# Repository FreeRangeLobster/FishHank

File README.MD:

# Description
This embedded system is designed to control control devices used in a fish tank, thies Includes but is not limited to lights, filter pumps, air pumps, CO2 reactors, UV lights and others. The system is capable of controllng 8 channels 220V AC up to 2A each 

The system is also equiped with the following systems: 
	-SD card
	-Real time clock
	-Bluetooth connection
	-flash memory 
	-temperature sensor. 
	
This devices are available to be connected to any IOT terminal, which could be a Raspberry pi or a ESP32 or a ST Nucleo. for this iteration it was selected an ESP32 WRoom 32.

## Weapons of choice
Embedded System ESP32	: Visual Studio Code with platform IO
Aux IO Control syste 	: Visual Studio Code with platform IO
Supervisory system   	: Visual Studio .net C# and WPF
Supervisory system 		: Mosquitto and NodeRed- Running on Raspberry pi(Experimetal)
PCB Development     	: Eagle
Comms to 3rd party		: ESP32 TCP Server/Client
Fast prototyping    	:Arduino IDE 1.6
Source Control and housekeeping: GitHub 

## PCB BOM
See parts schedule file 

## Production Files
Files submited to produce PCB

## PCB
Schematic and PCB files. Developed using Eagle

## Supervisory and config App
Developed using c#

## Images
Schematic

PCB

Format: 

## Libraries
Libraries developed and downloaded for the pcb integration

RTC
GetTimeNumber
GetTimeString
SetTimeString
CalculateFutureTimeCheck

OLED
DrawTable
ShowStatus
ShowTemperature
ShowOutputs
ShowTime
InitialDisplayShow

SD
FindEvent(CurrentTime)
GetStatus
GetConfiguration
DumpEvents

INPUTOUTPUT CONTROLLER 
GetStatus
SetOutputTo(OutputNumber,State)
GetInputs
ClearEvent
ClearOutputs

## Export
This folder contains 1:1 export views of the PCB

## Datasheets
Datasheets of the components used in the PCB

## Arduino Code
Developed to test the SSRs and User Inputs

# To Do is To Be 
|Status|ID|Description|
| ------ | ------ | ------ |
|DONE|1|Populate and test the PSU, test for shrt circuit and protectionsn |
|DONE|2|Populate and test One channel the SSR system |DONE|
|DONE|3|Populate and test microcontroller |
|DONE|4|populate and test bluetooth DONE |
|DONE|5|sd card reader DONE |
|DONE|6|realtime clock DONE |
|DONE|7|Temperature DONE |
|DONE|8|Make APIs libraries to deal with peripherals |
|DONE|9|add ALL days event |
|DONE|10|Tidy up oled screen, clear display square before writing output |
|DONE|11|test bluetooth debugging messages|
|DONE|12|mod the arduino auc board to update and toggle output|
|DONE|13|add Auto/Manual switch to the controller|
||14|Apply loads and test outputs|
|DONE|15|Rearrange outputs in arduino aux|
|DONE|16|Read IOAux output state|
|DONE|17|Test using Bluetooth|
|DONE|18|Test Application|
||19|Add the leds to the NodeRed|
|DONE|20|Top acrilic cover to test mains|
||21|Modify and update PCB layout and components-See notes in logbook|
|DONE|22|Tidy up code, files and merge to master|
|DONE|24|Double check and record GPIOs schedule ESP32-DevKit| 
||25|Get enclosure out of fishtank and replace components|
||26||
||27||
||28||
||29||
||30||
||31||
||32||
||33||
||34||
||35||

# To Do is To Be Embedded system- Code implementation
| API | Function | Implemented | Tested Works | Doesnt work | Not Tested | Notes | 
| ------ | ------ | ------ | ------ | ------ | ------ | ----------------------------------- | 
|RTC  |GetTimeNumber 	| YES |YES|  |  |  |
|RTC  |GetTimeString 	| YES |YES|  |  |  |
|RTC  |SetTimeString 	| YES |YES|  |  |  |
|OLED |DrawTable     	|YES  |YES  |  |  |  |
|OLED |ShowStatus  		|YES|YES|  |  |  |
|OLED |ShowTemperature 	| YES |YES|  |  |  |
|OLED |ShowOutputs 		|YES  |YES|  |  |  |
|OLED |ShowTime 		|YES|YES |  |  |  |
|OLED |InitialDisplayShow | YES |YES |  |  |  |
|OLED |CalculateFutureTimeCheck | YES |YES  |  |  |  |
|SD   |FindEvent(CurrentTime) |YES|YES  |  |  |  |
|SD   |GetStatus		| YES |YES  |  |  |  |
|SD   |GetConfiguration	|  YES|YES  |  |  |  |
|SD   |DumpEvents		| YES 	| YES|  |  |  |
|IO Ctrl|GetStatus		| YES | YES |  |  |  |
|IO Ctrl|SetOutputTo(OutputNumber,State)| YES |YES  |  |  |  |
|IO Ctrl|ClearInputEvent| NA |  |  |  | NA as IOCtrl updates automatic   |
|IO Ctrl|ClearOutputs| NA|  |  |  | Covered in Set Output To |

# Commands
? Help
K Initialise
I Idle
N Update Screen
M Check Events
O Update Outputs
D Delete Memory
0 Read Page Number 0_0000
1 AddEvent  1_1030WED31
2 Disable Event  2_001
3 Trace ON
4 Update Output 4_11 Output 1 ON
5 Write Status on OLED 5_Hello
6 Set Time RTC 6_DDMMY_HHmmss
7 Read Time
8 Check Current Event
9 Trace OFF

# PCB Upgrades and Improvements
|Status|ID|Description|
| ------ | ------ | ------ |
||1|Remove JLCJLCJCL, manufacturer disregarded the notes |
||2|Git webpage is not legible, find a better place|
|DONE|3|Bluetooth pinout is back to front in the eagle pcb library|
||4|Transistor not BCE, evaluate to use another one- Wrong footprint|
|DONE|5|SSR Output changed to 150ohm for a 10K resistor, so far is working fine|
||6|Breakout connector pin 1 and 2 to be renamed. INT1-> 5V, INT2->3V|
||7|Footprint of SSR to be adjusted|
||8|Add level converters, BSS138|
||9|Add 2 additional LEDs to show stay alive signal|
||10|Change output numbers in PCB to make it more readable|
||11|Add ESP32-DevKit to the PCB|
||12|R_UTX1=Link, R_UTX2 = Not Fitted|
||13|Remove Flash memory|
||14|SD Card Feed 5V|
||15|Add Auto/Manual trhough the level converter|
|DONE|16|SD Card back to front|

### Cheatsheet
#### Git

Command | Description
--- | --- 
git fetch | gets the remote status of the repository
git status | display the local current status of the repository
git pull | updates changes in the local repository
git add . | updates (adds, removes) files and infor from local to remote repository
git commit -m "" | Commits the changes and allows for a message to be updated
git push origin master| Pushes changes to remote repository
git checkout --| Reverts the files to the last commited version
git reset --hard | UNDO local file changes and KEEP your last commit
 
git branch alphr | Creates a neew branch
git branch --list | List current branches
git checkout alphr | switch local head to printer
git branch | shows current branch
git push --set-upstream origin alphr| creates new branch and pushes to remote repository
git merge alphr| merges brench. first it is required to go to master by checkout master

special thanks to for the atmega library
https://github.com/njh/eagle-library
https://github.com/sparkfun/SparkFun-Eagle-Libraries

#### Controller Pins
Top View 

 Down conting from top - Right
GND    -> GND 
GPIO23 -> MOSI SD Card
GPIO22 -> I2C SCL Oled and RTC 
GPIO1  -> 
GPIO3  -> 
GPIO21 -> I2C SDA Oled and RTC
GND    -> 
GPIO19 -> MISO SD Card
GPIO18 -> CLK SD Card
GPIO5  -> Chip Select SD Card
GPIO17 -> Serial2 TX IO Controller 
GPIO16 -> Serial2 RX IO Controller
GPIO4  -> Serial2 RX Bluetooth
GPIO0  -> 
GPIO2  -> Serial2 TX Bluetooth
GPIO15 -> Temp 1 Wire
GPIO8  ->
GPIO7  ->
GPIO6  ->
3v3
USB Connection

down conting from top - Left
3v3    -> Level Shifter Power
EN     -> 
GPIO36 -> New Event IOCtrl
GPIO39 ->
GPIO34 ->
GPIO35 ->
GPIO32 ->
GPIO33 ->
GPIO25 ->
GPIO26 ->
GPIO27 -> 
GPIO14 ->
GPIO12 ->
GND    ->
GPIO13 ->
GPIO9  ->
GPIO10 ->
GPIO11 ->
VIN    -> 
USB Connection to PC

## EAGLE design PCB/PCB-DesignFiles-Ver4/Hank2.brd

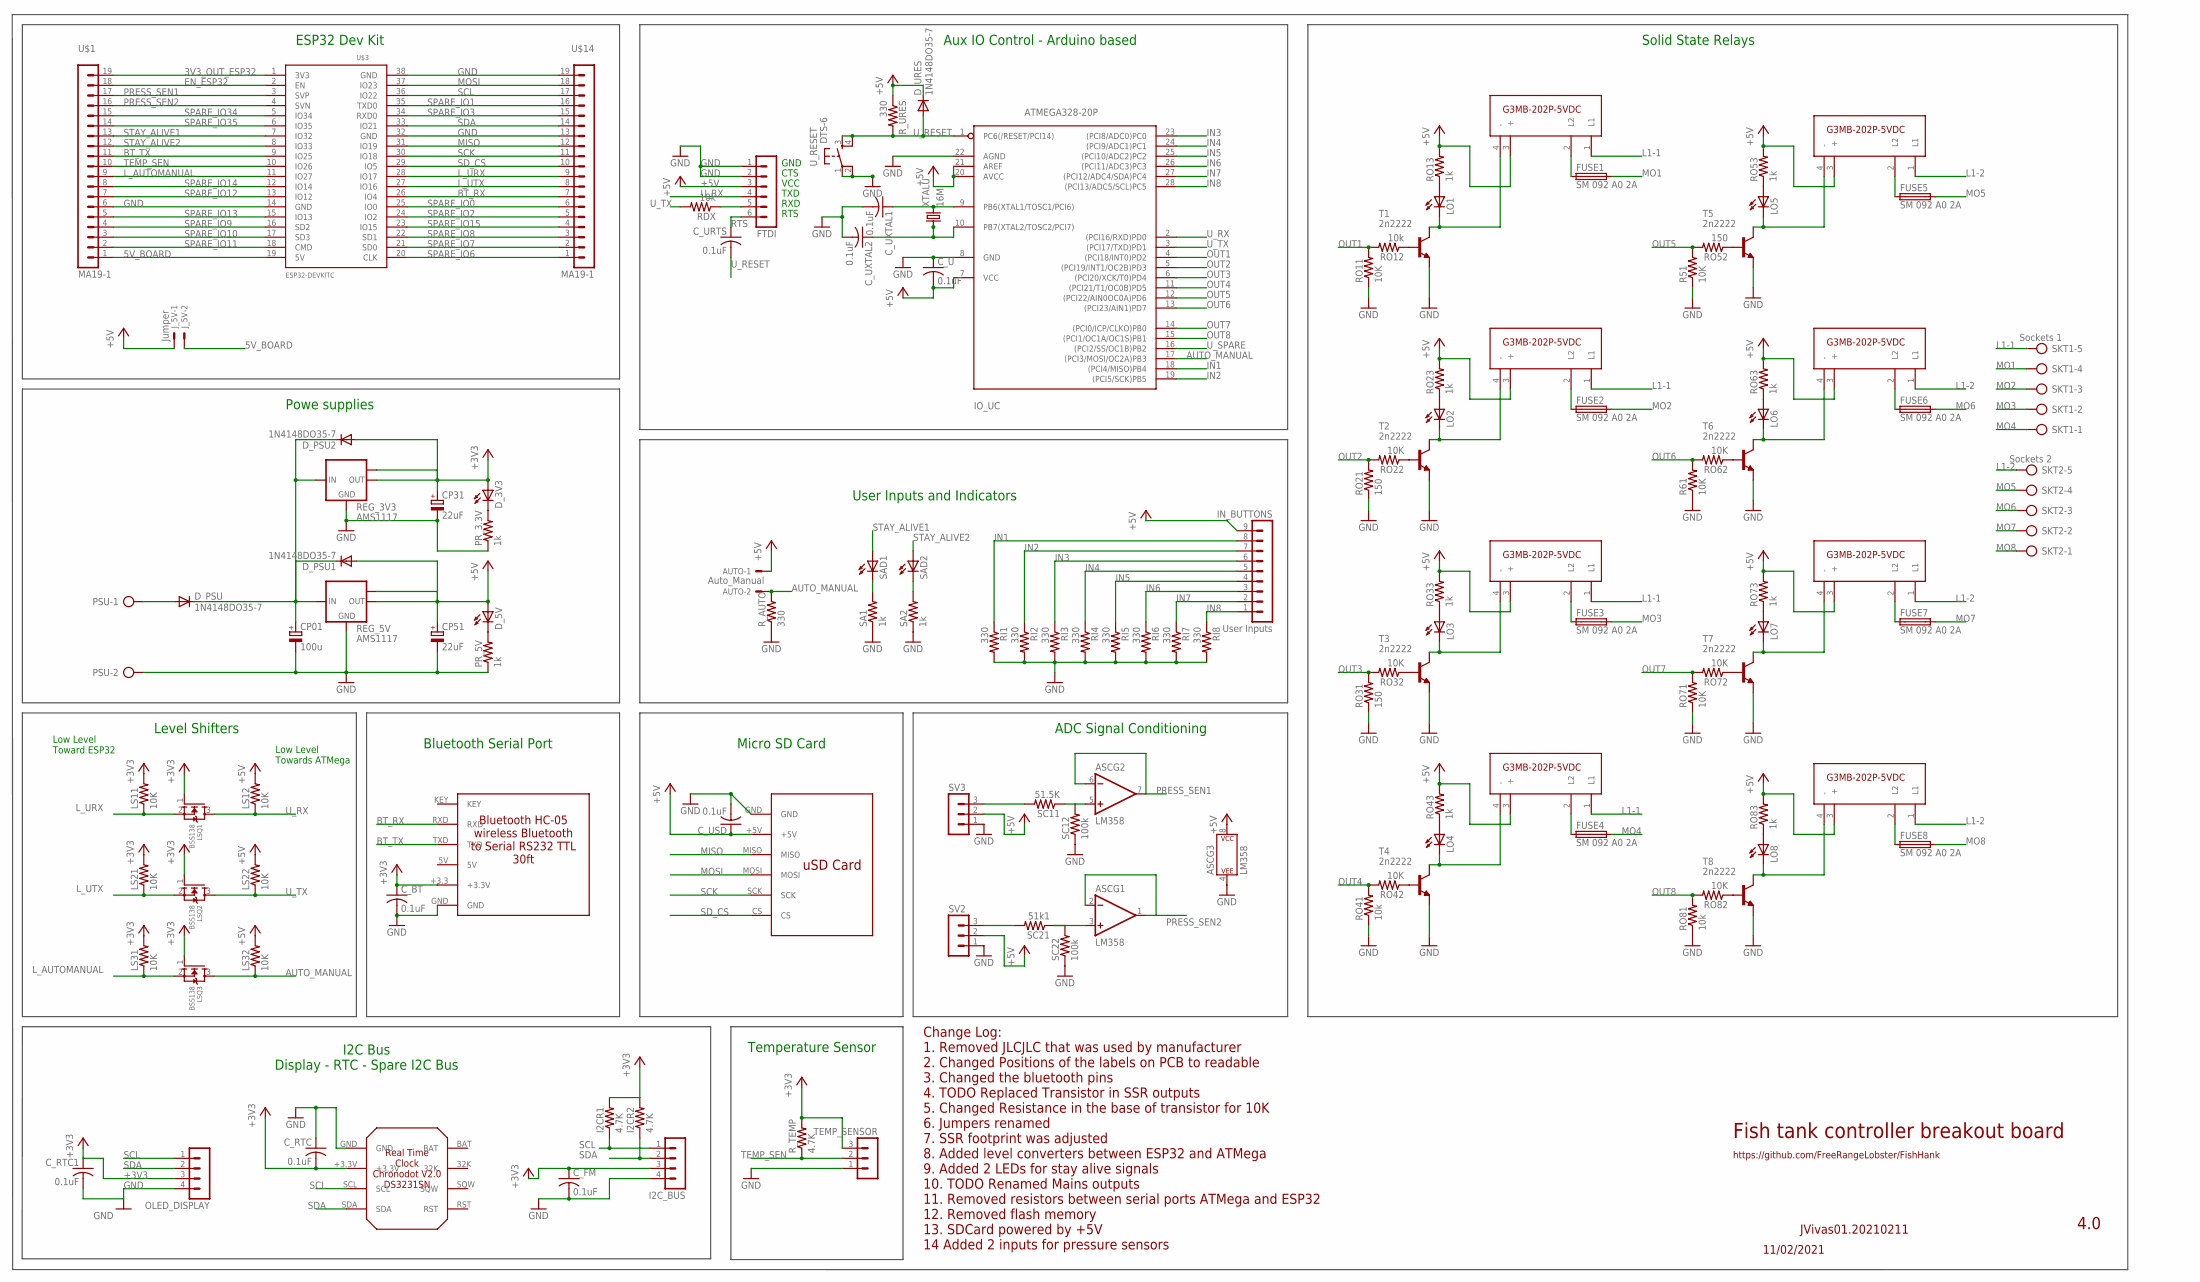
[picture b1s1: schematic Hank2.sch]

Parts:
ASC: LM358; DIP08
AUTO: Auto_Manual; 22-23-2021
CP01: 100u; E2,5-6
CP31, CP51: 22uF; E2,5-6
C_BT: 0.1uF; C025-024X044
C_FM: 0.1uF; C025-024X044
C_RTC, C_RTC1: 0.1uF; C025-024X044
C_U: 0.1uF; C025-024X044
C_URTS: 0.1uF; C025-024X044
C_USD: 0.1uF; C025-024X044
C_UXTAL1, C_UXTAL2: 0.1uF; C025-024X044
D_3V3, D_5V: LED3MM
D_PSU, D_PSU1, D_PSU2: 1N4148DO35-7; DO35-7
D_URES: 1N4148DO35-7; DO35-7
FTDI: MA06-1
FUSE1, FUSE2, FUSE3, FUSE4, FUSE5, FUSE6, FUSE7, FUSE8: SM 092 A0 2A; PICOFUSE
I2CR1, I2CR2: 4.7K; 0207/10
I2C_BUS: MA04-1
IN_BUTTONS: User Inputs; MA09-1
IO_UC: ATMEGA328-20P; DIL28-3
J_5V: Jumper; 22-23-2021
LO1, LO2, LO3, LO4, LO5, LO6, LO7, LO8: LED3MM
LS11, LS12, LS21, LS22, LS31, LS32: 10K; 0207/10
LSQ1, LSQ2, LSQ3: BSS138; SOT23
OLED_DISPLAY: MA04-1
PR_3.3V, PR_5V: 1k; 0207/10
PSU: AK500/2
R51, R61: 10K; 0207/10
RDX: 10k; 0207/10
REG_3V3, REG_5V: AMS1117; SOT223
RI1, RI2, RI3, RI4, RI5, RI6, RI7, RI8: 330; 0207/10
RO11, RO22, RO32, RO42, RO62, RO71, RO72, RO82: 10K; 0207/10
RO12, RO41, RO81: 10k; 0207/10
RO13, RO23, RO33, RO43, RO53, RO63, RO73, RO83: 1k; 0207/10
RO21, RO31, RO52: 150; 0207/10
R_AUTO: 330; 0207/10
R_TEMP: 4.7K; 0207/10
R_URES: 330; 0207/10
SA1, SA2: 1k; 0207/10
SAD1, SAD2: LED3MM
SC11: 51.5K; 0207/10
SC12, SC22: 100k; 0207/10
SC21: 51k1; 0207/10
SKT1: Sockets 1; AK500/5
SKT2: Sockets 2; AK500/5
SV2, SV3: MA03-1
T1, T2, T3, T4, T5, T6, T7, T8: 2n2222; TO92-ECB
TEMP_SENSOR: MA03-1
U$1, U$14: MA19-1
U$2: BLUETOOTH; BLUETOOTH_FOOTPRINT
U$3: ESP32DEVKITC; ESP32-DEVKITC
U$4, U$5, U$8, U$9, U$10, U$11, U$12, U$13: SSR; SSR_FOOTPRINT
U$6: RTC; RTC_FOOTPRINT
U$15: SD_CARD_READER; SD_CARD_READER_FOOTPRINT
U_RESET: DTS-6
XTALU: 16M; HC49/S

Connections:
2N2222_6: LO6.K (C), T6.C, U$11.4 (-); also elsewhere on the board
3V3_OUT_ESP32: U$1.19, U$3.1 (3V3)
5V_BOARD: J_5V.2, U$1.1, U$3.19 (5V)
+3V3: CP31.+, C_BT.1, C_FM.1, C_RTC.2, C_RTC1.1, D_3V3.A, D_PSU2.A, I2CR1.2, I2CR2.2, I2C_BUS.3, LS11.2, LS21.2, LS31.2, LSQ1.1 (G), LSQ2.1 (G), LSQ3.1 (G), OLED_DISPLAY.3, REG_3V3.2 (OUT), REG_3V3.TAB (OUT1), R_TEMP.2, TEMP_SENSOR.3, U$2.+3.3 (+3.3V), U$6.+3.3V
+5V: ASC.8 (P$V+), AUTO.1, CP51.+, C_U.2, C_USD.1, D_5V.A, D_PSU1.A, D_URES.C, FTDI.3, IN_BUTTONS.9, IO_UC.7 (VCC), IO_UC.20 (AVCC), IO_UC.21 (AREF), J_5V.1, LS12.2, LS22.2, LS32.2, REG_5V.2 (OUT), REG_5V.TAB (OUT1), RO13.2, RO23.2, RO33.2, RO43.2, RO53.2, RO63.2, RO73.2, RO83.2, R_URES.1, SV2.2, SV3.2, U$4.3 (+), U$5.3 (+), U$8.3 (+), U$9.3 (+), U$10.3 (+), U$11.3 (+), U$12.3 (+), U$13.3 (+), U$15.+5V
AUTO_MANUAL: AUTO.2, IO_UC.17 ((PCI3/MOSI/OC2A)PB3), LS32.1, LSQ3.3 (D), R_AUTO.2
BT_RX: U$2.RXD, U$3.26 (IO4), U$14.7
BT_TX: U$1.11, U$2.TXD, U$3.9 (IO25)
CP12: CP01.+, D_PSU.C, D_PSU1.C, D_PSU2.C, REG_3V3.3 (IN), REG_5V.3 (IN)
EN_ESP32: U$1.18, U$3.2 (EN)
GND: ASC.4 (P$V-), CP01.-, CP31.-, CP51.-, C_BT.2, C_FM.2, C_RTC.1, C_RTC1.2, C_U.1, C_USD.2, C_UXTAL1.2, C_UXTAL2.2, FTDI.1, FTDI.2, I2C_BUS.4, IO_UC.8 (GND), IO_UC.22 (AGND), OLED_DISPLAY.4, PR_3.3V.1, PR_5V.1, PSU.2, R51.1, R61.1, REG_3V3.1 (GND), REG_5V.1 (GND), RI1.2, RI2.2, RI3.2, RI4.2, RI5.2, RI6.2, RI7.2, RI8.2, RO11.1, RO21.1, RO31.1, RO41.1, RO71.1, RO81.1, R_AUTO.1, SA1.1, SA2.1, SC12.1, SC22.1, SV2.1, SV3.1, T1.E, T2.E, T3.E, T4.E, T5.E, T6.E, T7.E, T8.E, TEMP_SENSOR.1, U$1.6, U$2.GND, U$3.14 (GND), U$3.32 (GND), U$3.38 (GND), U$6.GND, U$14.13, U$14.19, U$15.GND, U_RESET.1, U_RESET.2; also elsewhere on the board
IN1: IN_BUTTONS.8, IO_UC.18 ((PCI4/MISO)PB4), RI1.1
IN2: IN_BUTTONS.7, IO_UC.19 ((PCI5/SCK)PB5), RI2.1
IN3: IN_BUTTONS.6, IO_UC.23 ((PCI8/ADC0)PC0), RI3.1
IN4: IN_BUTTONS.5, IO_UC.24 ((PCI9/ADC1)PC1), RI4.1
IN5: IN_BUTTONS.4, IO_UC.25 ((PCI10/ADC2)PC2), RI5.1
IN6: IN_BUTTONS.3, IO_UC.26 ((PCI11/ADC3)PC3), RI6.1
IN7: IN_BUTTONS.2, IO_UC.27 ((PCI12/ADC4/SDA)PC4), RI7.1
IN8: IN_BUTTONS.1, IO_UC.28 ((PCI13/ADC5/SCL)PC5), RI8.1
L1-1: SKT1.5, U$4.1 (L1), U$5.1 (L1), U$8.1 (L1), U$10.1 (L1)
L1-2: SKT2.5, U$9.1 (L1), U$11.1 (L1), U$12.1 (L1), U$13.1 (L1)
LED2: SA2.2, SAD2.K (C)
L_AUTOMANUAL: LS31.1, LSQ3.2 (S), U$1.9, U$3.11 (IO27)
L_O1: LO2.K (C), T2.C, U$8.4 (-); also elsewhere on the board
L_O3: LO3.K (C), T3.C, U$5.4 (-); also elsewhere on the board
L_URX: LS11.1, LSQ1.2 (S), U$3.28 (IO17), U$14.9
L_UTX: LS21.1, LSQ2.2 (S), U$3.27 (IO16), U$14.8
MISO: U$3.31 (IO19), U$14.12, U$15.MISO
MO1: FUSE1.2, SKT1.4
MO2: FUSE2.2, SKT1.3
MO3: FUSE3.2, SKT1.2
MO4: FUSE4.2, SKT1.1
MO5: FUSE5.2, SKT2.4
MO6: FUSE6.2, SKT2.3
MO7: FUSE7.2, SKT2.2
MO8: FUSE8.2, SKT2.1
MOSI: U$3.37 (IO23), U$14.18, U$15.MOSI
unnamed 37: RO12.1, T1.B; also elsewhere on the board
unnamed: FUSE1.1, U$4.2 (L2)
unnamed: D_5V.K (C), PR_5V.2
unnamed: D_3V3.K (C), PR_3.3V.2
unnamed: SA1.2, SAD1.K (C)
unnamed: D_PSU.A, PSU.1
unnamed 43: RO52.1, T5.B; also elsewhere on the board
unnamed 44: RO62.1, T6.B; also elsewhere on the board
unnamed: FUSE8.1, U$13.2 (L2)
unnamed: LO5.A, RO53.1
unnamed 47: LO5.K (C), T5.C, U$9.4 (-); also elsewhere on the board
unnamed: FUSE7.1, U$12.2 (L2)
unnamed: FUSE2.1, U$8.2 (L2)
unnamed: FUSE3.1, U$5.2 (L2)
unnamed: LO6.A, RO63.1
unnamed 52: RO22.1, T2.B; also elsewhere on the board
unnamed: FUSE6.1, U$11.2 (L2)
unnamed: LO7.A, RO73.1
unnamed 55: LO7.K (C), T7.C, U$12.4 (-); also elsewhere on the board
unnamed 56: RO72.1, T7.B; also elsewhere on the board
unnamed 57: RO32.1, T3.B; also elsewhere on the board
unnamed: FUSE4.1, U$10.2 (L2)
unnamed: LO8.A, RO83.1
unnamed 60: LO8.K (C), T8.C, U$13.4 (-); also elsewhere on the board
unnamed 61: RO42.1, T4.B; also elsewhere on the board
unnamed: FUSE5.1, U$9.2 (L2)
unnamed: LO1.A, RO13.1
unnamed 64: LO1.K (C), T1.C, U$4.4 (-); also elsewhere on the board
unnamed 65: RO82.1, T8.B; also elsewhere on the board
unnamed: C_UXTAL1.1, IO_UC.9 (PB6(XTAL1/TOSC1/PCI6)), XTALU.2
unnamed: LO2.A, RO23.1
unnamed: C_UXTAL2.1, IO_UC.10 (PB7(XTAL2/TOSC2/PCI7)), XTALU.1
unnamed: LO3.A, RO33.1
unnamed: SC21.2, SV2.3
unnamed: LO4.A, RO43.1
unnamed 72: LO4.K (C), T4.C, U$10.4 (-); also elsewhere on the board
unnamed: ASC.5 (+IN), SC11.1, SC12.2
unnamed: ASC.3 (+IN), SC21.1, SC22.2
unnamed: SC11.2, SV3.3
OUT1: IO_UC.4 ((PCI18/INT0)PD2), RO11.2, RO12.2
OUT2: IO_UC.5 ((PCI19/INT1/OC2B)PD3), RO21.2, RO22.2
OUT3: IO_UC.6 ((PCI20/XCK/T0)PD4), RO31.2, RO32.2
OUT4: IO_UC.11 ((PCI21/T1/OC0B)PD5), RO41.2, RO42.2
OUT5: IO_UC.12 ((PCI22/AIN0OC0A)PD6), R51.2, RO52.2
OUT6: IO_UC.13 ((PCI23/AIN1)PD7), R61.2, RO62.2
OUT7: IO_UC.14 ((PCI0/ICP/CLKO)PB0), RO71.2, RO72.2
OUT8: IO_UC.15 ((PCI1/OC1A/OC1S)PB1), RO81.2, RO82.2
PRESS_SEN1: ASC.6 (-IN), ASC.7 (OUT), U$1.17, U$3.3 (SVP)
PRESS_SEN2: ASC.1 (OUT), ASC.2 (-IN), U$1.16, U$3.4 (SVN)
RTS: C_URTS.1, FTDI.6
SCK: U$3.30 (IO18), U$14.11, U$15.SCK
SCL: I2CR1.1, I2C_BUS.1, OLED_DISPLAY.1, U$3.36 (IO22), U$6.SCL, U$14.17
SDA: I2CR2.1, I2C_BUS.2, OLED_DISPLAY.2, U$3.33 (IO21), U$6.SDA, U$14.14
SD_CS: U$3.29 (IO5), U$14.10, U$15.CS
SPARE_IO0: U$3.25 (IO0), U$14.6
SPARE_IO1: U$3.35 (TXD0), U$14.16
SPARE_IO2: U$3.24 (IO2), U$14.5
SPARE_IO3: U$3.34 (RXD0), U$14.15
SPARE_IO6: U$3.20 (CLK), U$14.1
SPARE_IO7: U$3.21 (SD0), U$14.2
SPARE_IO8: U$3.22 (SD1), U$14.3
SPARE_IO9: U$1.4, U$3.16 (SD2)
SPARE_IO10: U$1.3, U$3.17 (SD3)
SPARE_IO11: U$1.2, U$3.18 (CMD)
SPARE_IO12: U$1.7, U$3.13 (IO12)
SPARE_IO13: U$1.5, U$3.15 (IO13)
SPARE_IO14: U$1.8, U$3.12 (IO14)
SPARE_IO15: U$3.23 (IO15), U$14.4
SPARE_IO34: U$1.15, U$3.5 (IO34)
SPARE_IO35: U$1.14, U$3.6 (IO35)
STAY_ALIVE1: SAD1.A, U$1.13, U$3.7 (IO32)
STAY_ALIVE2: SAD2.A, U$1.12, U$3.8 (IO33)
TEMP_SEN: R_TEMP.1, TEMP_SENSOR.2, U$1.10, U$3.10 (IO26)
UTX: FTDI.5, RDX.1
U_RESET: C_URTS.2, D_URES.A, IO_UC.1 (PC6(/RESET/PCI14)), R_URES.2, U_RESET.3, U_RESET.4
U_RX: FTDI.4, IO_UC.2 ((PCI16/RXD)PD0), LS12.1, LSQ1.3 (D)
U_SPARE: IO_UC.16 ((PCI2/SS/OC1B)PB2)
U_TX: IO_UC.3 ((PCI17/TXD)PD1), LS22.1, LSQ2.3 (D), RDX.2

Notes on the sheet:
https://github.com/FreeRangeLobster/FishHank
Fish tank controller breakout board
CTS
GND
VCC
TXD
RXD
RTS
Low Level Toward ESP32
Low Level Towards ATMega
Level Shifters
ESP32 Dev Kit
Powe supplies
ADC Signal Conditioning
Solid State Relays
Aux IO Control - Arduino based
User Inputs and Indicators
I2C Bus Display - RTC - Spare I2C Bus
Temperature Sensor
Micro SD Card
Bluetooth Serial Port
4.0
11/02/2021
JVivas01.20210211
Change Log: 1. Removed JLCJLC that was used by manufacturer 2. Changed Positions of the labels on PCB to readable 3. Changed the bluetooth pins 4. TODO Replaced Transistor in SSR outputs 5. Changed Resistance in the base of transistor for 10K 6. Jumpers renamed 7. SSR footprint was adjusted 8. Adde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

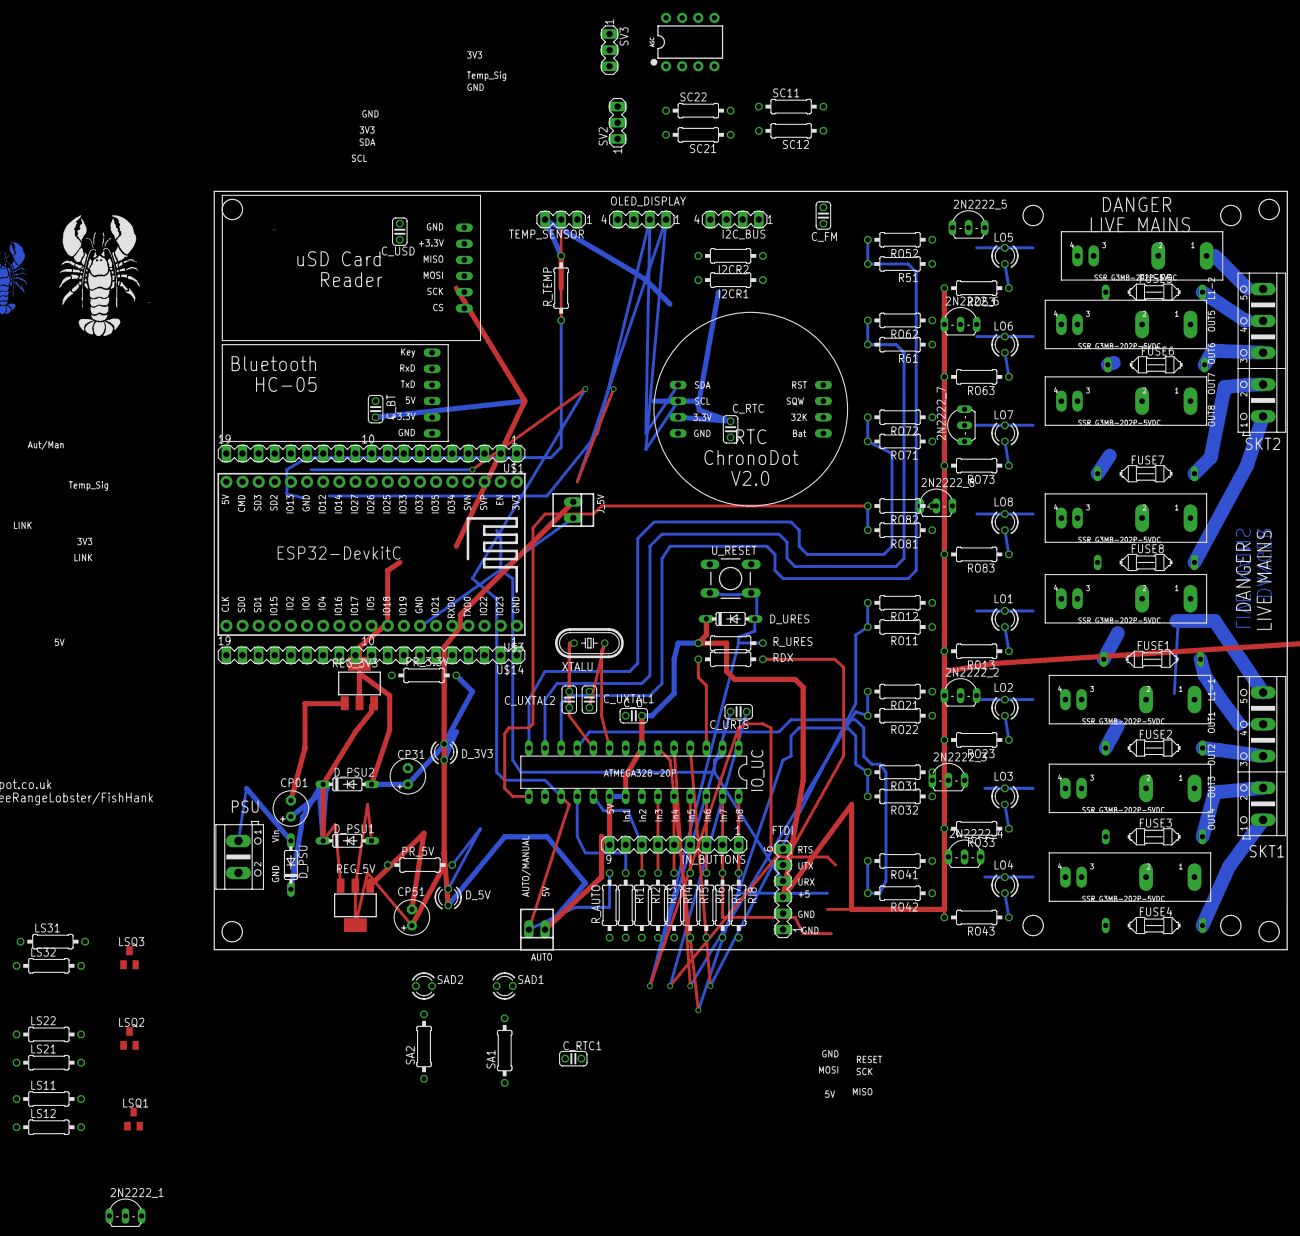
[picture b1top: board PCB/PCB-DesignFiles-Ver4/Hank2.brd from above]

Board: 2 copper layers, 168.9 x 119.4 mm, 131 parts (0 on the bottom side), 114 nets.

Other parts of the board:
2N2222_1, 2N2222_2, 2N2222_3, 2N2222_4, 2N2222_5, 2N2222_6, 2N2222_7, 2N2222_8: TO92-EBC

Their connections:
2N2222_6: 2N2222_6.C; also elsewhere on the board
GND: 2N2222_1.E, 2N2222_2.E, 2N2222_3.E, 2N2222_4.E, 2N2222_5.E, 2N2222_6.E, 2N2222_7.E, 2N2222_8.E; also elsewhere on the board
L_O1: 2N2222_2.C; also elsewhere on the board
L_O3: 2N2222_3.C; also elsewhere on the board
unnamed 37: 2N2222_1.B; also elsewhere on the board
unnamed 43: 2N2222_5.B; also elsewhere on the board
unnamed 44: 2N2222_6.B; also elsewhere on the board
unnamed 47: 2N2222_5.C; also elsewhere on the board
unnamed 52: 2N2222_2.B; also elsewhere on the board
unnamed 55: 2N2222_7.C; also elsewhere on the board
unnamed 56: 2N2222_7.B; also elsewhere on the board
unnamed 57: 2N2222_3.B; also elsewhere on the board
unnamed 60: 2N2222_8.C; also elsewhere on the board
unnamed 61: 2N2222_4.B; also elsewhere on the board
unnamed 64: 2N2222_1.C; also elsewhere on the board
unnamed 65: 2N2222_8.B; also elsewhere on the board
unnamed 72: 2N2222_4.C; also elsewhere on the board

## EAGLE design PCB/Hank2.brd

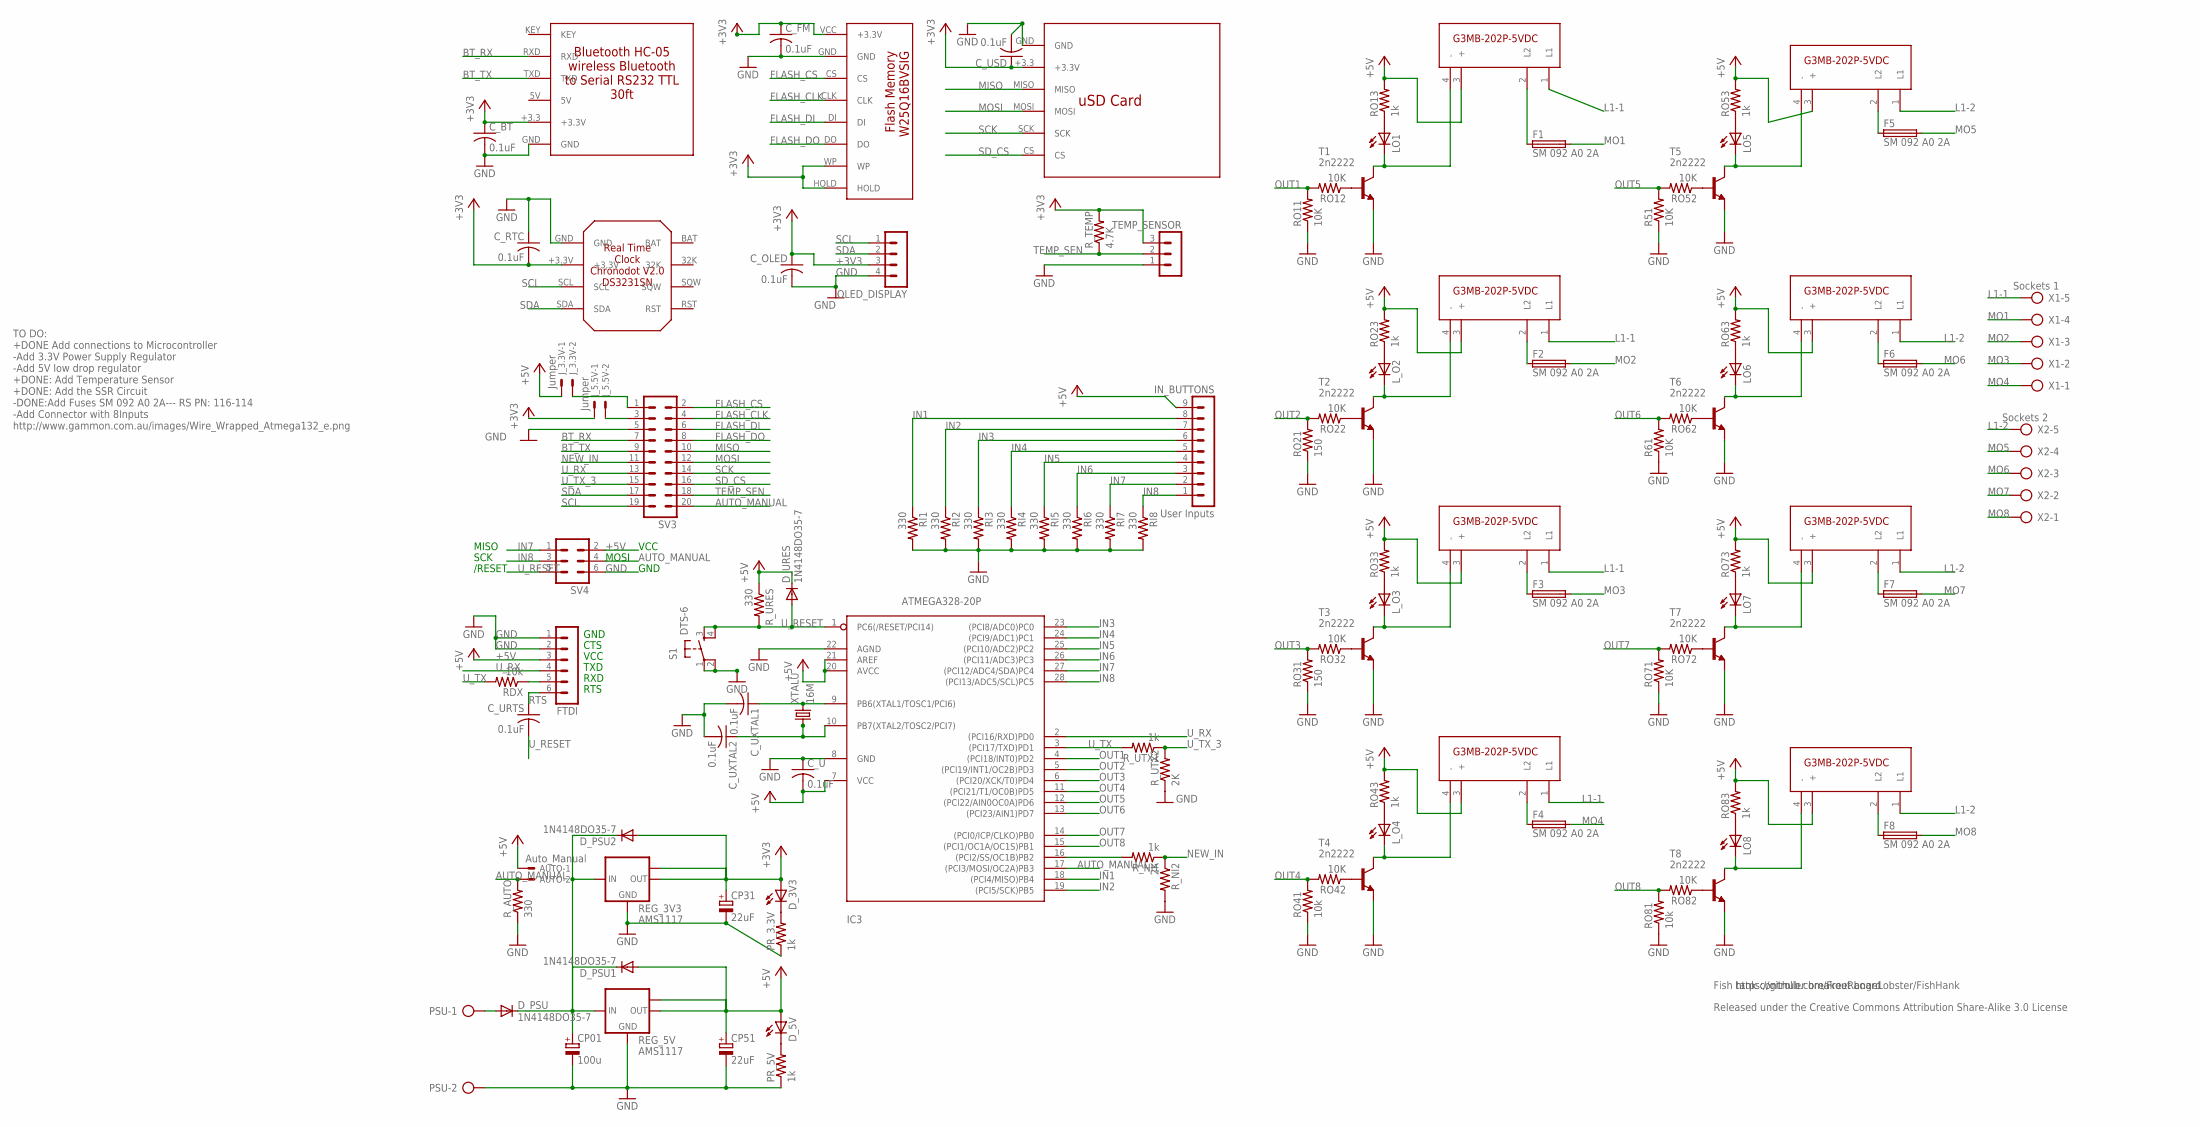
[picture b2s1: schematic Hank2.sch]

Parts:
AUTO: Auto_Manual; 22-23-2021
CP01: 100u; E2,5-6
CP31, CP51: 22uF; E2,5-6
C_BT: 0.1uF; C025-024X044
C_FM: 0.1uF; C025-024X044
C_OLED: 0.1uF; C025-024X044
C_RTC: 0.1uF; C025-024X044
C_U: 0.1uF; C025-024X044
C_URTS: 0.1uF; C025-024X044
C_USD: 0.1uF; C025-024X044
C_UXTAL1, C_UXTAL2: 0.1uF; C025-024X044
D_3V3, D_5V: LED3MM
D_PSU, D_PSU1, D_PSU2: 1N4148DO35-7; DO35-7
D_URES: 1N4148DO35-7; DO35-7
F1, F2, F3, F4, F5, F6, F7, F8: SM 092 A0 2A; PICOFUSE
FTDI: MA06-1
IC3: ATMEGA328-20P; DIL28-3
IN_BUTTONS: User Inputs; MA09-1
J_3.3V, J_5.5V: Jumper; 22-23-2021
LO1, LO5, LO6, LO7, LO8: LED3MM
L_O2, L_O3, L_O4: LED3MM
OLED_DISPLAY: MA04-1
PR_3.3V, PR_5V: 1k; 0207/10
PSU: AK500/2
R51, R61: 10K; 0207/10
RDX: 10k; 0207/10
REG_3V3, REG_5V: AMS1117; SOT223
RI1, RI2, RI3, RI4, RI5, RI6, RI7, RI8: 330; 0207/10
RO11, RO12, RO22, RO32, RO42, RO52, RO62, RO71, RO72, RO82: 10K; 0207/10
RO13, RO23, RO33, RO43, RO53, RO63, RO73, RO83: 1k; 0207/10
RO21, RO31: 150; 0207/10
RO41, RO81: 10k; 0207/10
R_AUTO: 330; 0207/10
R_NI1: 1k; 0207/10
R_NI2: 2K; 0207/10
R_TEMP: 4.7K; 0207/10
R_URES: 330; 0207/10
R_UTX1: 1k; 0207/10
R_UTX2: 2K; 0207/10
S1: DTS-6
SSR1, SSR2, SSR3, SSR4, SSR5, SSR6, SSR7, SSR8: SSR; SSR_FOOTPRINT
SV3: MA10-2
SV4: MA03-2
T1, T2, T3, T4, T5, T6, T7, T8: 2n2222; TO92-ECB
TEMP_SENSOR: MA03-1
U$1: FLASH_MEMORY; FLASHMEMORY_FOOTPRINT
U$4: BLUETOOTH; BLUETOOTH_FOOTPRINT
U$6: RTC; RTC_FOOTPRINT
U$7: SD_CARD_READER; SD_CARD_READER_FOOTPRINT
X1: Sockets 1; AK500/5
X2: Sockets 2; AK500/5
XTALU: 16M; HC49/S

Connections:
+3V3: CP31.+, C_BT.1, C_FM.1, C_OLED.1, C_RTC.2, C_USD.1, D_3V3.A, D_PSU2.A, J_5.5V.1, OLED_DISPLAY.3, REG_3V3.2 (OUT), REG_3V3.TAB (OUT1), R_TEMP.2, TEMP_SENSOR.3, U$1.HOLD, U$1.VCC (+3.3V), U$1.WP, U$4.+3.3 (+3.3V), U$6.+3.3V, U$7.+3.3 (+3.3V)
+5V: AUTO.1, CP51.+, C_U.2, D_5V.A, D_PSU1.A, D_URES.C, FTDI.3, IC3.7 (VCC), IC3.20 (AVCC), IC3.21 (AREF), IN_BUTTONS.9, J_3.3V.1, REG_5V.2 (OUT), REG_5V.TAB (OUT1), RO13.2, RO23.2, RO33.2, RO43.2, RO53.2, RO63.2, RO73.2, RO83.2, R_URES.1, SSR1.3 (+), SSR2.3 (+), SSR3.3 (+), SSR4.3 (+), SSR5.3 (+), SSR6.3 (+), SSR7.3 (+), SSR8.3 (+), SV4.2
AUTO_MANUAL: AUTO.2, IC3.17 ((PCI3/MOSI/OC2A)PB3), R_AUTO.2, SV3.20, SV4.4
BT_RX: SV3.7, U$4.RXD
BT_TX: SV3.9, U$4.TXD
CP12: CP01.+, D_PSU.C, D_PSU1.C, D_PSU2.C, REG_3V3.3 (IN), REG_5V.3 (IN)
FLASH_CLK: SV3.4, U$1.CLK
FLASH_CS: SV3.2, U$1.CS
FLASH_DI: SV3.6, U$1.DI
FLASH_DO: SV3.8, U$1.DO
GND: CP01.-, CP31.-, CP51.-, C_BT.2, C_FM.2, C_OLED.2, C_RTC.1, C_U.1, C_USD.2, C_UXTAL1.2, C_UXTAL2.2, FTDI.1, FTDI.2, IC3.8 (GND), IC3.22 (AGND), OLED_DISPLAY.4, PR_3.3V.1, PR_5V.1, PSU.2, R51.1, R61.1, REG_3V3.1 (GND), REG_5V.1 (GND), RI1.2, RI2.2, RI3.2, RI4.2, RI5.2, RI6.2, RI7.2, RI8.2, RO11.1, RO21.1, RO31.1, RO41.1, RO71.1, RO81.1, R_AUTO.1, R_NI2.2, R_UTX2.1, S1.1, S1.2, SV3.5, SV4.6, T1.E, T2.E, T3.E, T4.E, T5.E, T6.E, T7.E, T8.E, TEMP_SENSOR.1, U$1.GND, U$4.GND, U$6.GND, U$7.GND
IN1: IC3.18 ((PCI4/MISO)PB4), IN_BUTTONS.8, RI1.1
IN2: IC3.19 ((PCI5/SCK)PB5), IN_BUTTONS.7, RI2.1
IN3: IC3.23 ((PCI8/ADC0)PC0), IN_BUTTONS.6, RI3.1
IN4: IC3.24 ((PCI9/ADC1)PC1), IN_BUTTONS.5, RI4.1
IN5: IC3.25 ((PCI10/ADC2)PC2), IN_BUTTONS.4, RI5.1
IN6: IC3.26 ((PCI11/ADC3)PC3), IN_BUTTONS.3, RI6.1
IN7: IC3.27 ((PCI12/ADC4/SDA)PC4), IN_BUTTONS.2, RI7.1, SV4.1
IN8: IC3.28 ((PCI13/ADC5/SCL)PC5), IN_BUTTONS.1, RI8.1, SV4.3
L1-1: SSR1.1 (L1), SSR2.1 (L1), SSR3.1 (L1), SSR4.1 (L1), X1.5
L1-2: SSR5.1 (L1), SSR6.1 (L1), SSR7.1 (L1), SSR8.1 (L1), X2.5
L_O1: L_O2.K (C), SSR2.4 (-), T2.C
L_O3: L_O3.K (C), SSR3.4 (-), T3.C
MISO: SV3.10, U$7.MISO
MO1: F1.2, X1.4
MO2: F2.2, X1.3
MO3: F3.2, X1.2
MO4: F4.2, X1.1
MO5: F5.2, X2.4
MO6: F6.2, X2.3
MO7: F7.2, X2.2
MO8: F8.2, X2.1
MOSI: SV3.12, U$7.MOSI
unnamed: J_3.3V.2, SV3.1
unnamed: J_5.5V.2, SV3.3
unnamed: F1.1, SSR1.2 (L2)
unnamed: D_5V.K (C), PR_5V.2
unnamed: D_3V3.K (C), PR_3.3V.2
unnamed: D_PSU.A, PSU.1
unnamed: RO12.1, T1.B
unnamed: RO52.1, T5.B
unnamed: F8.1, SSR8.2 (L2)
unnamed: LO5.A, RO53.1
unnamed: LO5.K (C), SSR5.4 (-), T5.C
unnamed: F7.1, SSR7.2 (L2)
unnamed: F2.1, SSR2.2 (L2)
unnamed: F3.1, SSR3.2 (L2)
unnamed: LO6.A, RO63.1
unnamed: LO6.K (C), SSR6.4 (-), T6.C
unnamed: RO62.1, T6.B
unnamed: F6.1, SSR6.2 (L2)
unnamed: LO7.A, RO73.1
unnamed: LO7.K (C), SSR7.4 (-), T7.C
unnamed: RO72.1, T7.B
unnamed: RO42.1, T4.B
unnamed: F4.1, SSR4.2 (L2)
unnamed: LO8.A, RO83.1
unnamed: LO8.K (C), SSR8.4 (-), T8.C
unnamed: RO32.1, T3.B
unnamed: F5.1, SSR5.2 (L2)
unnamed: LO1.A, RO13.1
unnamed: LO1.K (C), SSR1.4 (-), T1.C
unnamed: RO22.1, T2.B
unnamed: C_UXTAL1.1, IC3.9 (PB6(XTAL1/TOSC1/PCI6)), XTALU.2
unnamed: L_O2.A, RO23.1
unnamed: RO82.1, T8.B
unnamed: C_UXTAL2.1, IC3.10 (PB7(XTAL2/TOSC2/PCI7)), XTALU.1
unnamed: L_O3.A, RO33.1
unnamed: IC3.16 ((PCI2/SS/OC1B)PB2), R_NI1.2
unnamed: L_O4.A, RO43.1
unnamed: L_O4.K (C), SSR4.4 (-), T4.C
NEW_IN: R_NI1.1, R_NI2.1, SV3.11
OUT1: IC3.4 ((PCI18/INT0)PD2), RO11.2, RO12.2
OUT2: IC3.5 ((PCI19/INT1/OC2B)PD3), RO21.2, RO22.2
OUT3: IC3.6 ((PCI20/XCK/T0)PD4), RO31.2, RO32.2
OUT4: IC3.11 ((PCI21/T1/OC0B)PD5), RO41.2, RO42.2
OUT5: IC3.12 ((PCI22/AIN0OC0A)PD6), R51.2, RO52.2
OUT6: IC3.13 ((PCI23/AIN1)PD7), R61.2, RO62.2
OUT7: IC3.14 ((PCI0/ICP/CLKO)PB0), RO71.2, RO72.2
OUT8: IC3.15 ((PCI1/OC1A/OC1S)PB1), RO81.2, RO82.2
RTS: C_URTS.1, FTDI.6
SCK: SV3.14, U$7.SCK
SCL: OLED_DISPLAY.1, SV3.19, U$6.SCL
SDA: OLED_DISPLAY.2, SV3.17, U$6.SDA
SD_CS: SV3.16, U$7.CS
TEMP_SEN: R_TEMP.1, SV3.18, TEMP_SENSOR.2
UTX: FTDI.5, RDX.1
U_RESET: C_URTS.2, D_URES.A, IC3.1 (PC6(/RESET/PCI14)), R_URES.2, S1.3, S1.4, SV4.5
U_RX: FTDI.4, IC3.2 ((PCI16/RXD)PD0), SV3.13
U_TX: IC3.3 ((PCI17/TXD)PD1), RDX.2, R_UTX1.2
U_TX_3: R_UTX1.1, R_UTX2.2, SV3.15

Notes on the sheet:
Released under the Creative Commons Attribution Share-Alike 3.0 License
https://github.com/FreeRangeLobster/FishHank
TO DO: +DONE Add connections to Microcontroller -Add 3.3V Power Supply Regulator -Add 5V low drop regulator +DONE: Add Temperature Sensor +DONE: Add the SSR Circuit -DONE:Add Fuses SM 092 A0 2A--- RS PN: 116-114 -Add Connector with 8Inputs http://www.gammon.com.au/images/Wire_Wrapped_Atmega132_e.png
Fish tank controller breakout board
CTS
GND
VCC
TXD
RXD
RTS
/RESET
SCK
MISO
MOSI

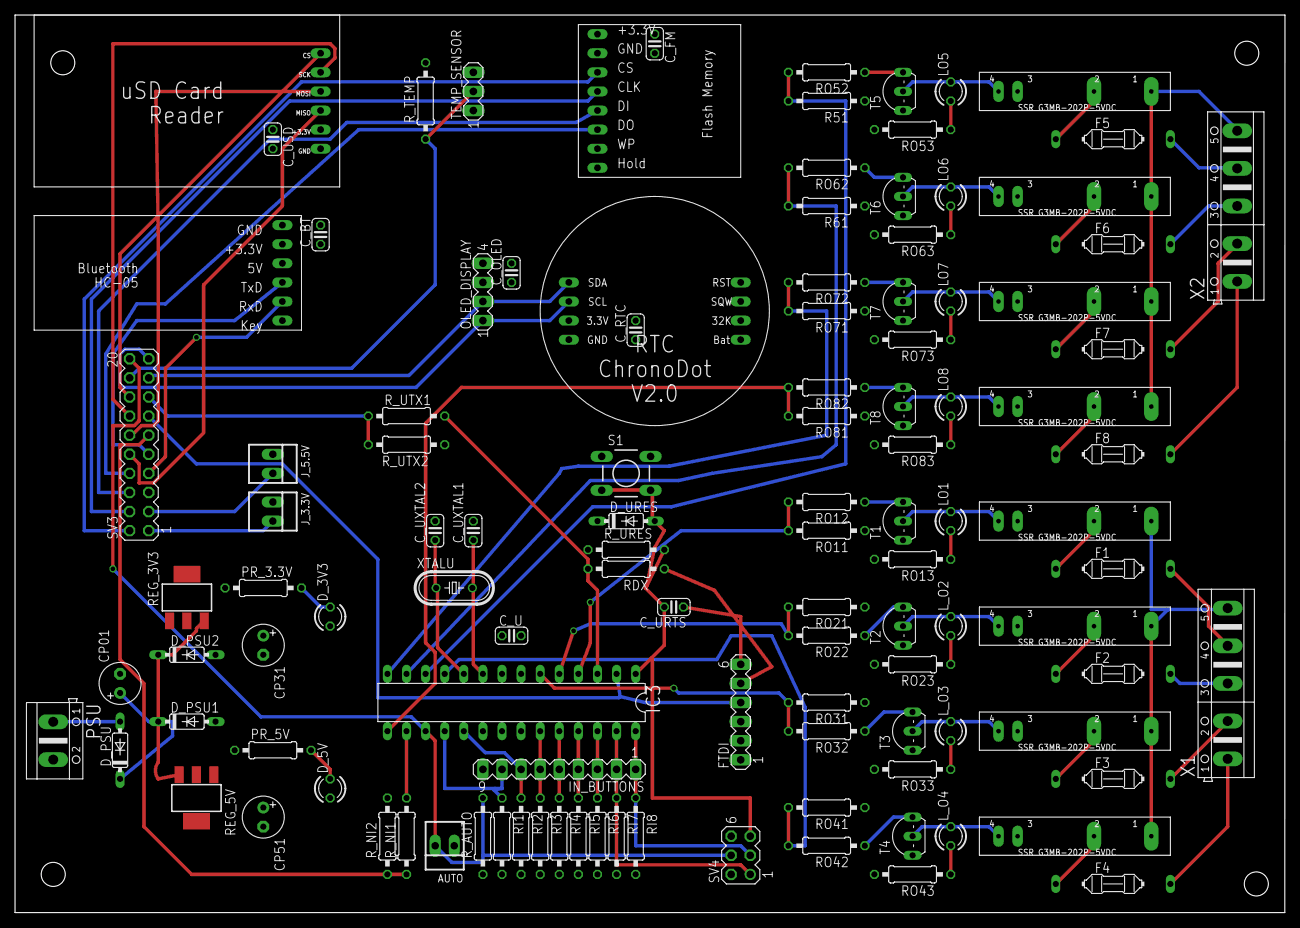
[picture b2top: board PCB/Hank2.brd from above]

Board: 2 copper layers, 168.9 x 119.4 mm, 113 parts (0 on the bottom side), 91 nets.

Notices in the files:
parts and their libraries:
SparkFun-IC-Amplifiers: Licensing: Creative Commons ShareAlike 4.0 International - https://creativecommons.org/licenses/by-sa/4.0
